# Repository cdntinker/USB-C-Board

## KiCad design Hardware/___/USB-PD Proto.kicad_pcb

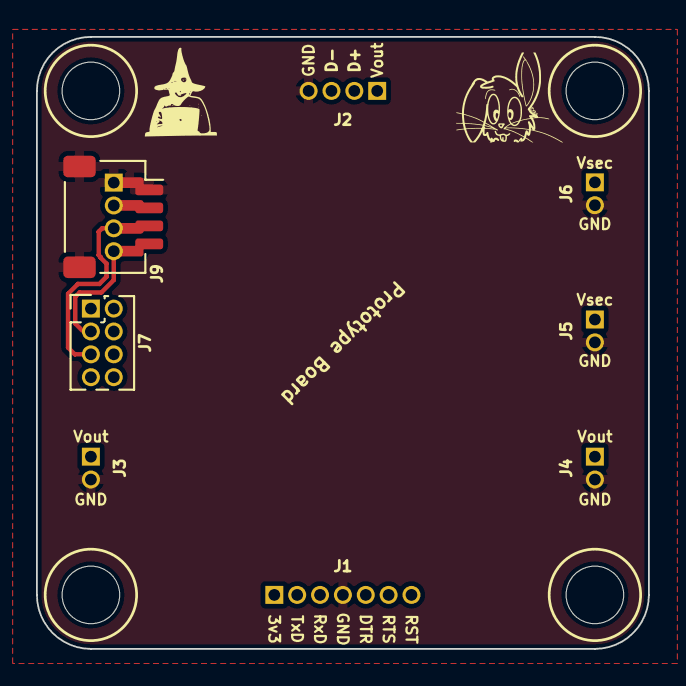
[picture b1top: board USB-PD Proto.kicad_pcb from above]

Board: 2 copper layers, 34.0 x 34.0 mm, 8 parts (0 on the bottom side), 3 nets.

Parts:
J1: Conn_01x07_Male; Board_Stacker_7
J2: Conn_01x04_Male; Board_Stacker_4
J3, J4, J5, J6: Conn_01x02_Male; Board_Stacker_2
J7: Conn_01x08_Male; PinHeader_2x04_P1.27mm_Vertical
J9: QWIIC_Stackable; QWIIC_Stack_II

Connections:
GND: J1.4, J2.4, J3.2, J4.2, J5.2, J6.2, J9.1, J9.MP (MountPin)
SCL: J7.3, J9.4
SDA: J7.5, J9.3
